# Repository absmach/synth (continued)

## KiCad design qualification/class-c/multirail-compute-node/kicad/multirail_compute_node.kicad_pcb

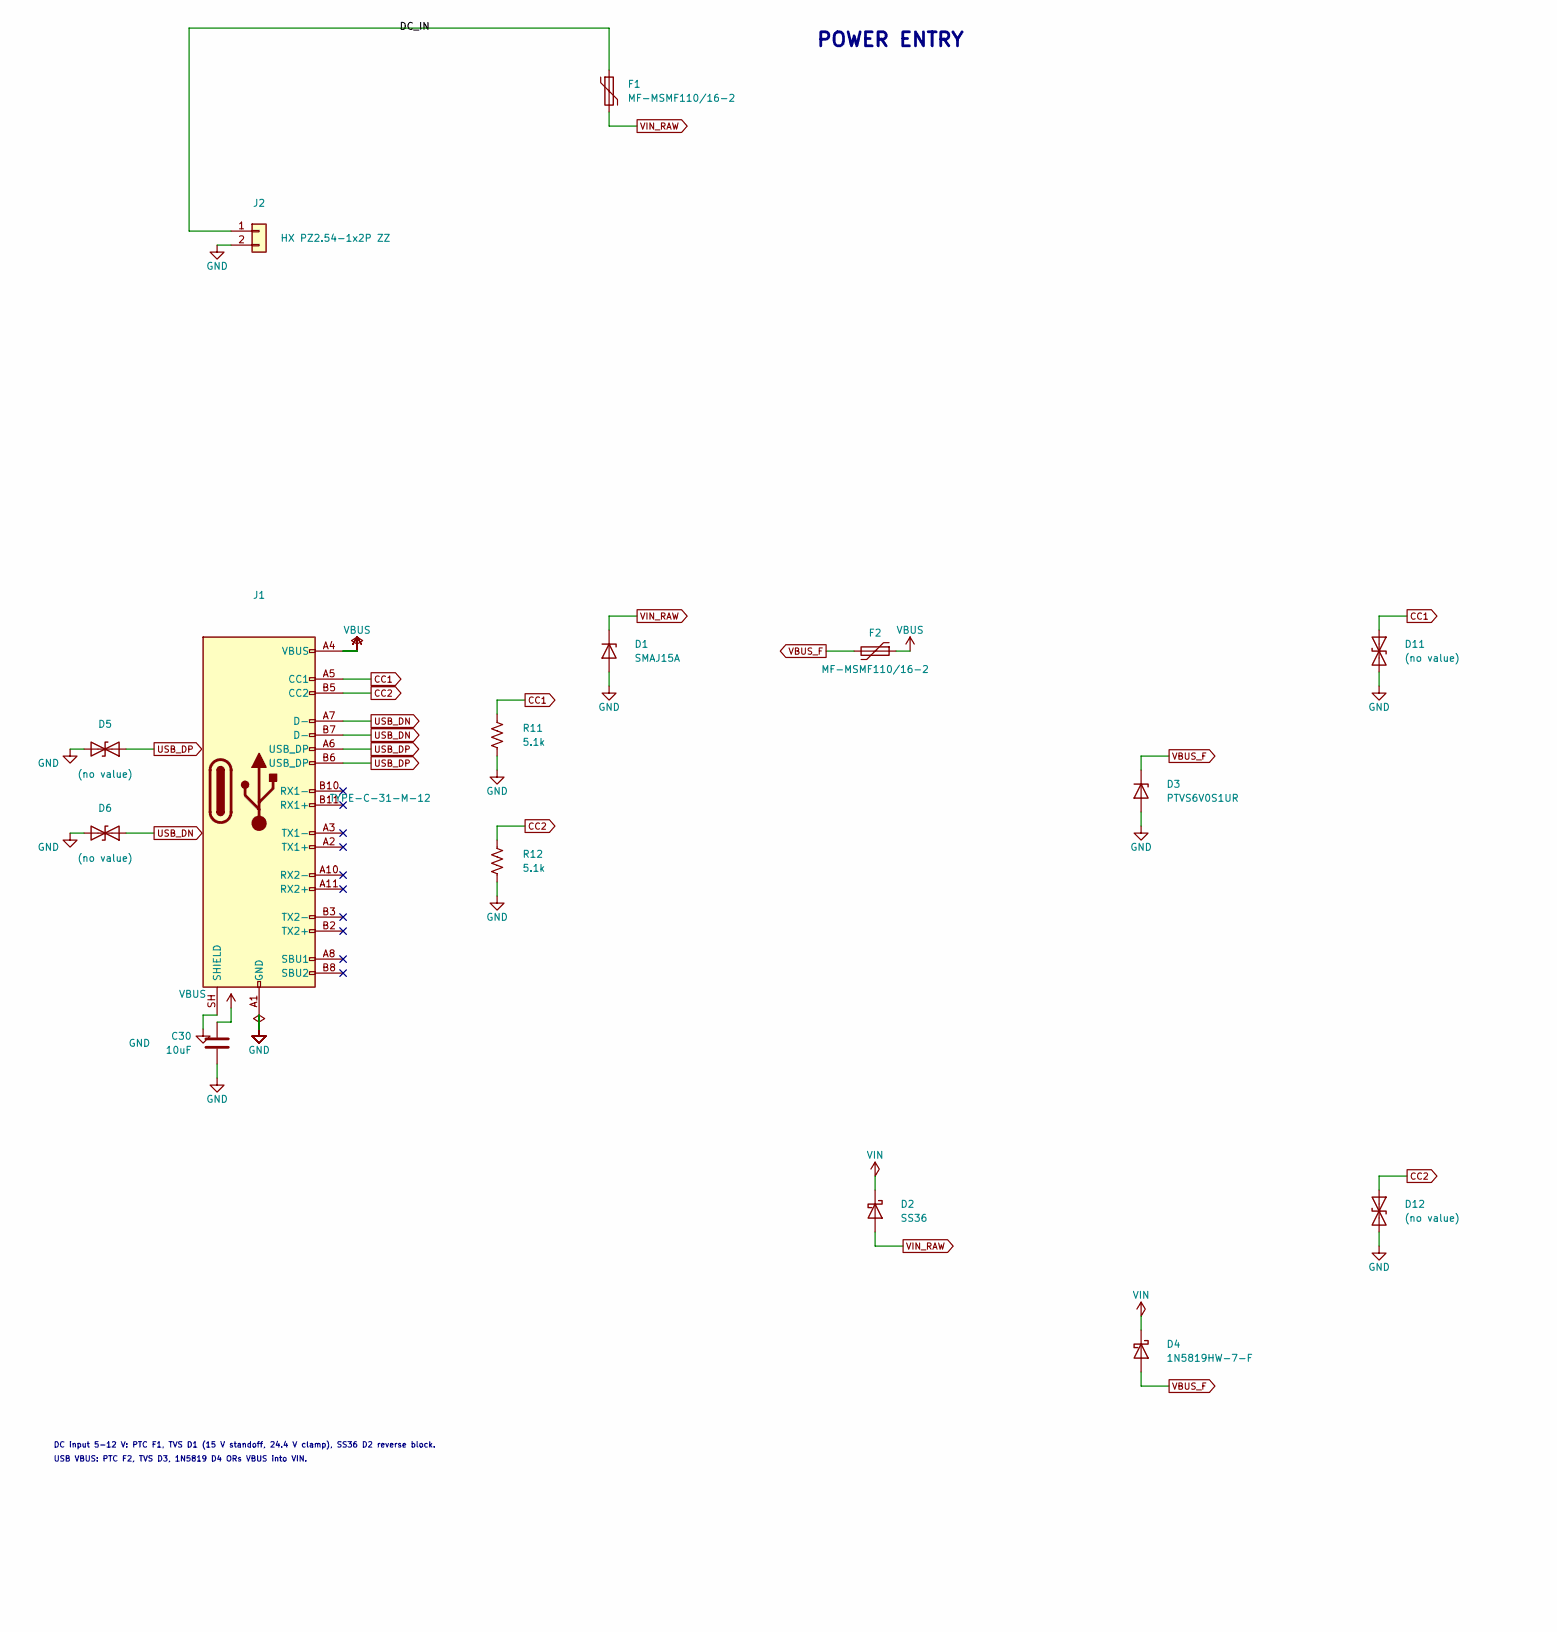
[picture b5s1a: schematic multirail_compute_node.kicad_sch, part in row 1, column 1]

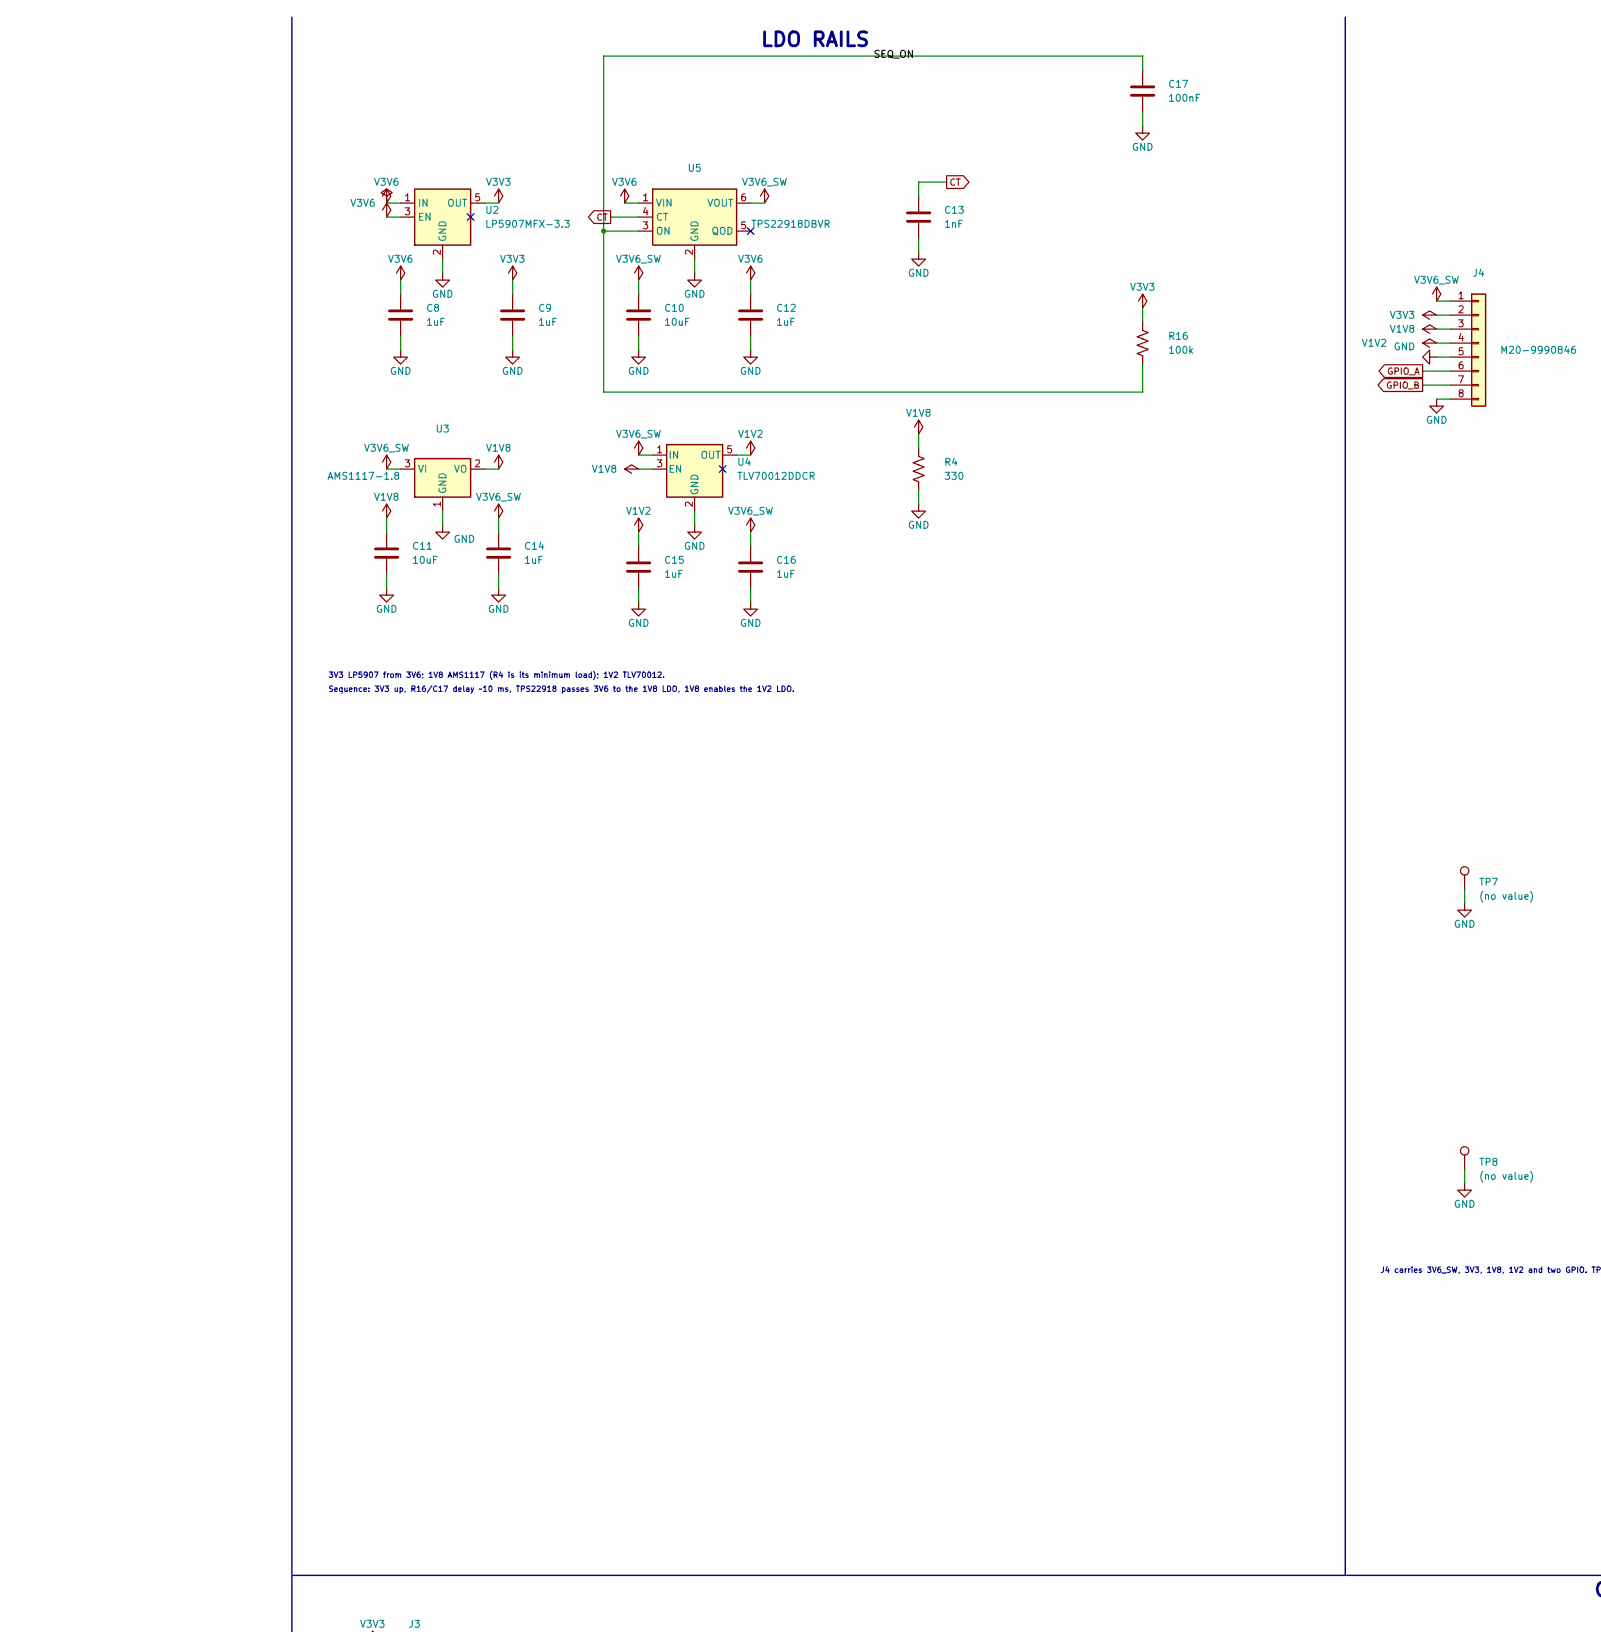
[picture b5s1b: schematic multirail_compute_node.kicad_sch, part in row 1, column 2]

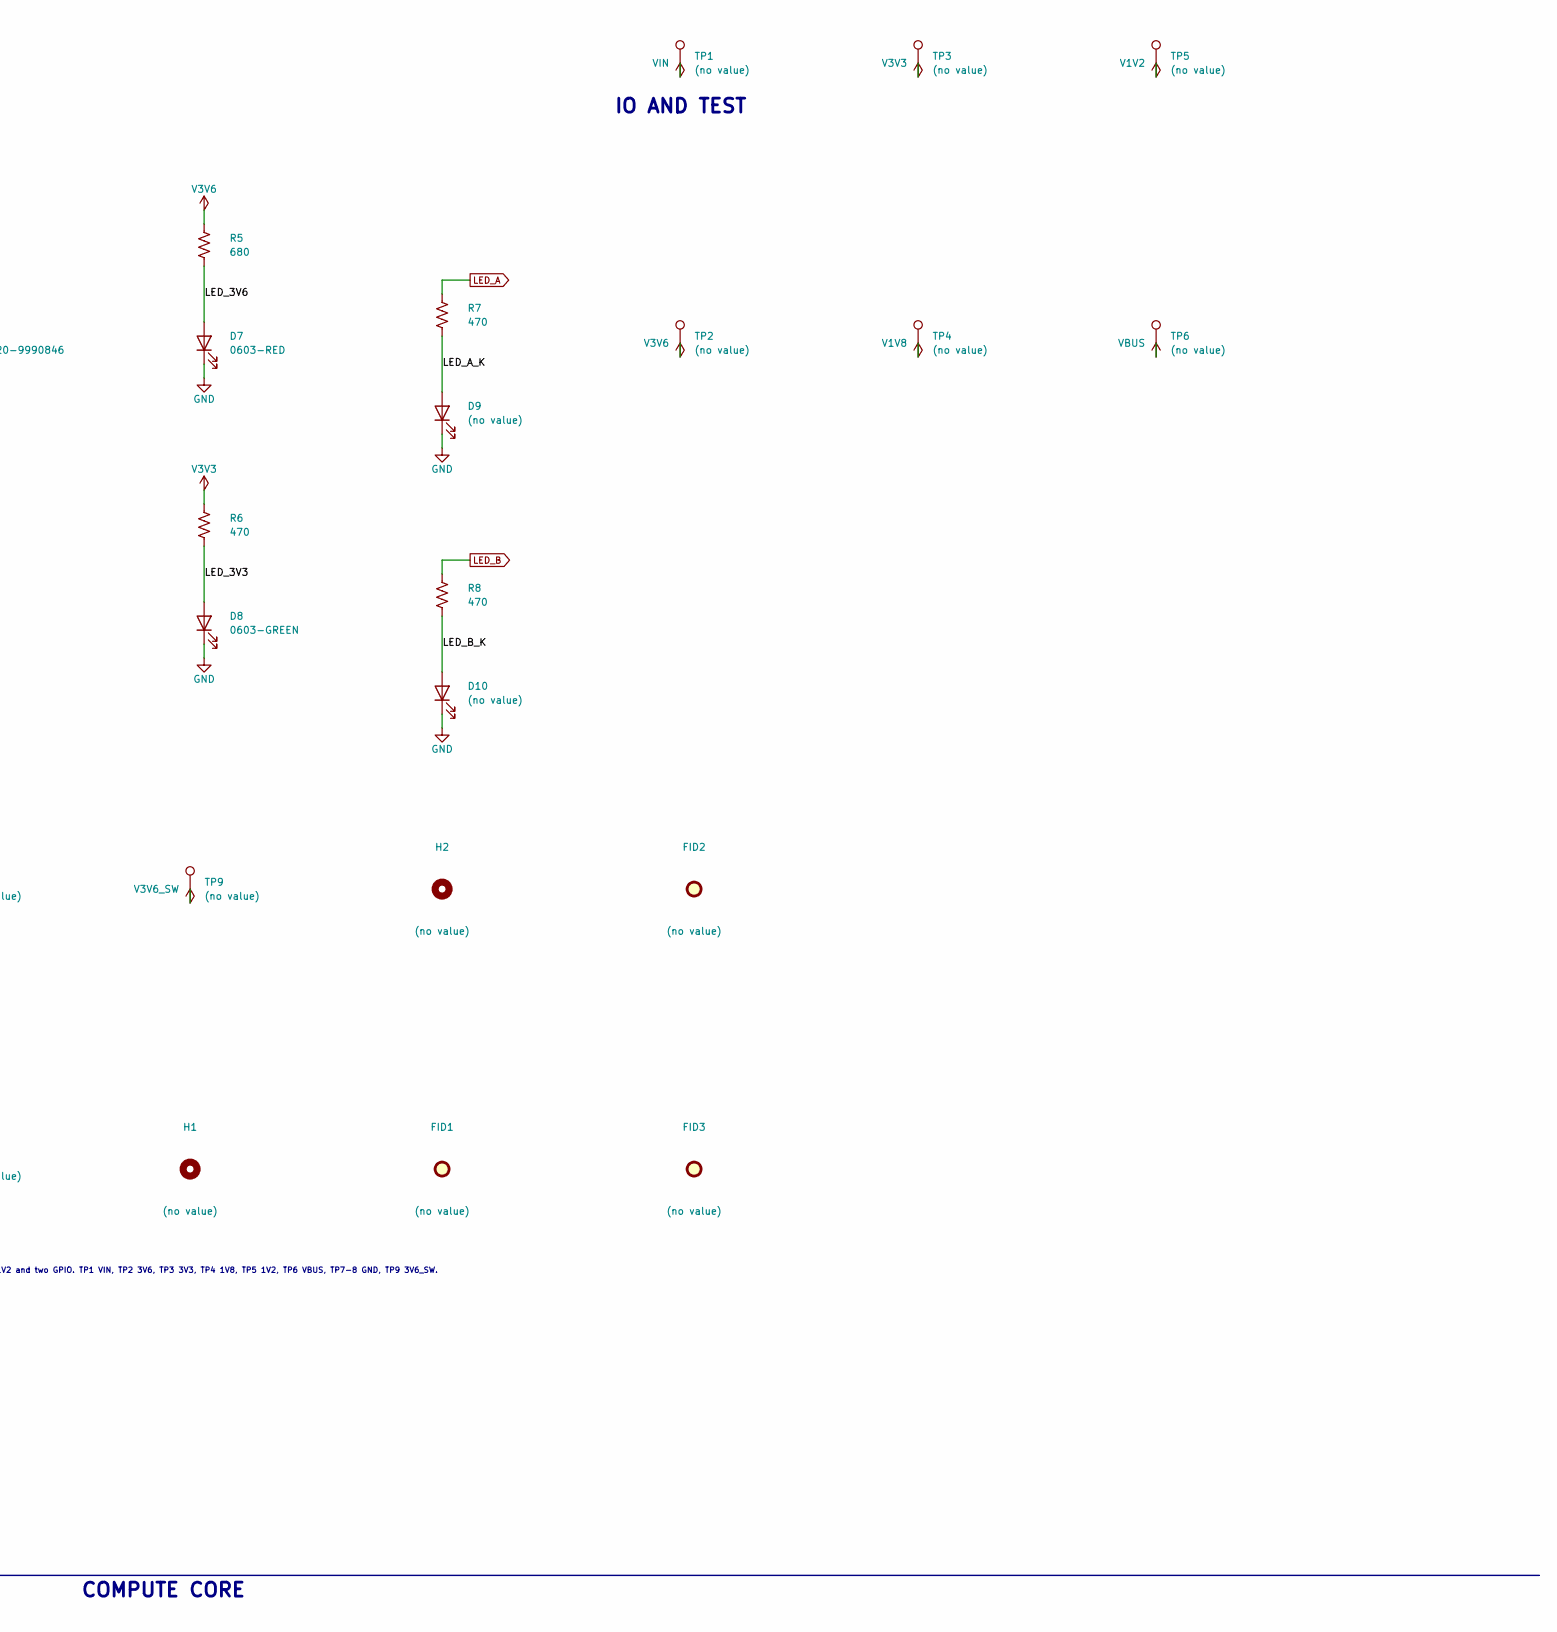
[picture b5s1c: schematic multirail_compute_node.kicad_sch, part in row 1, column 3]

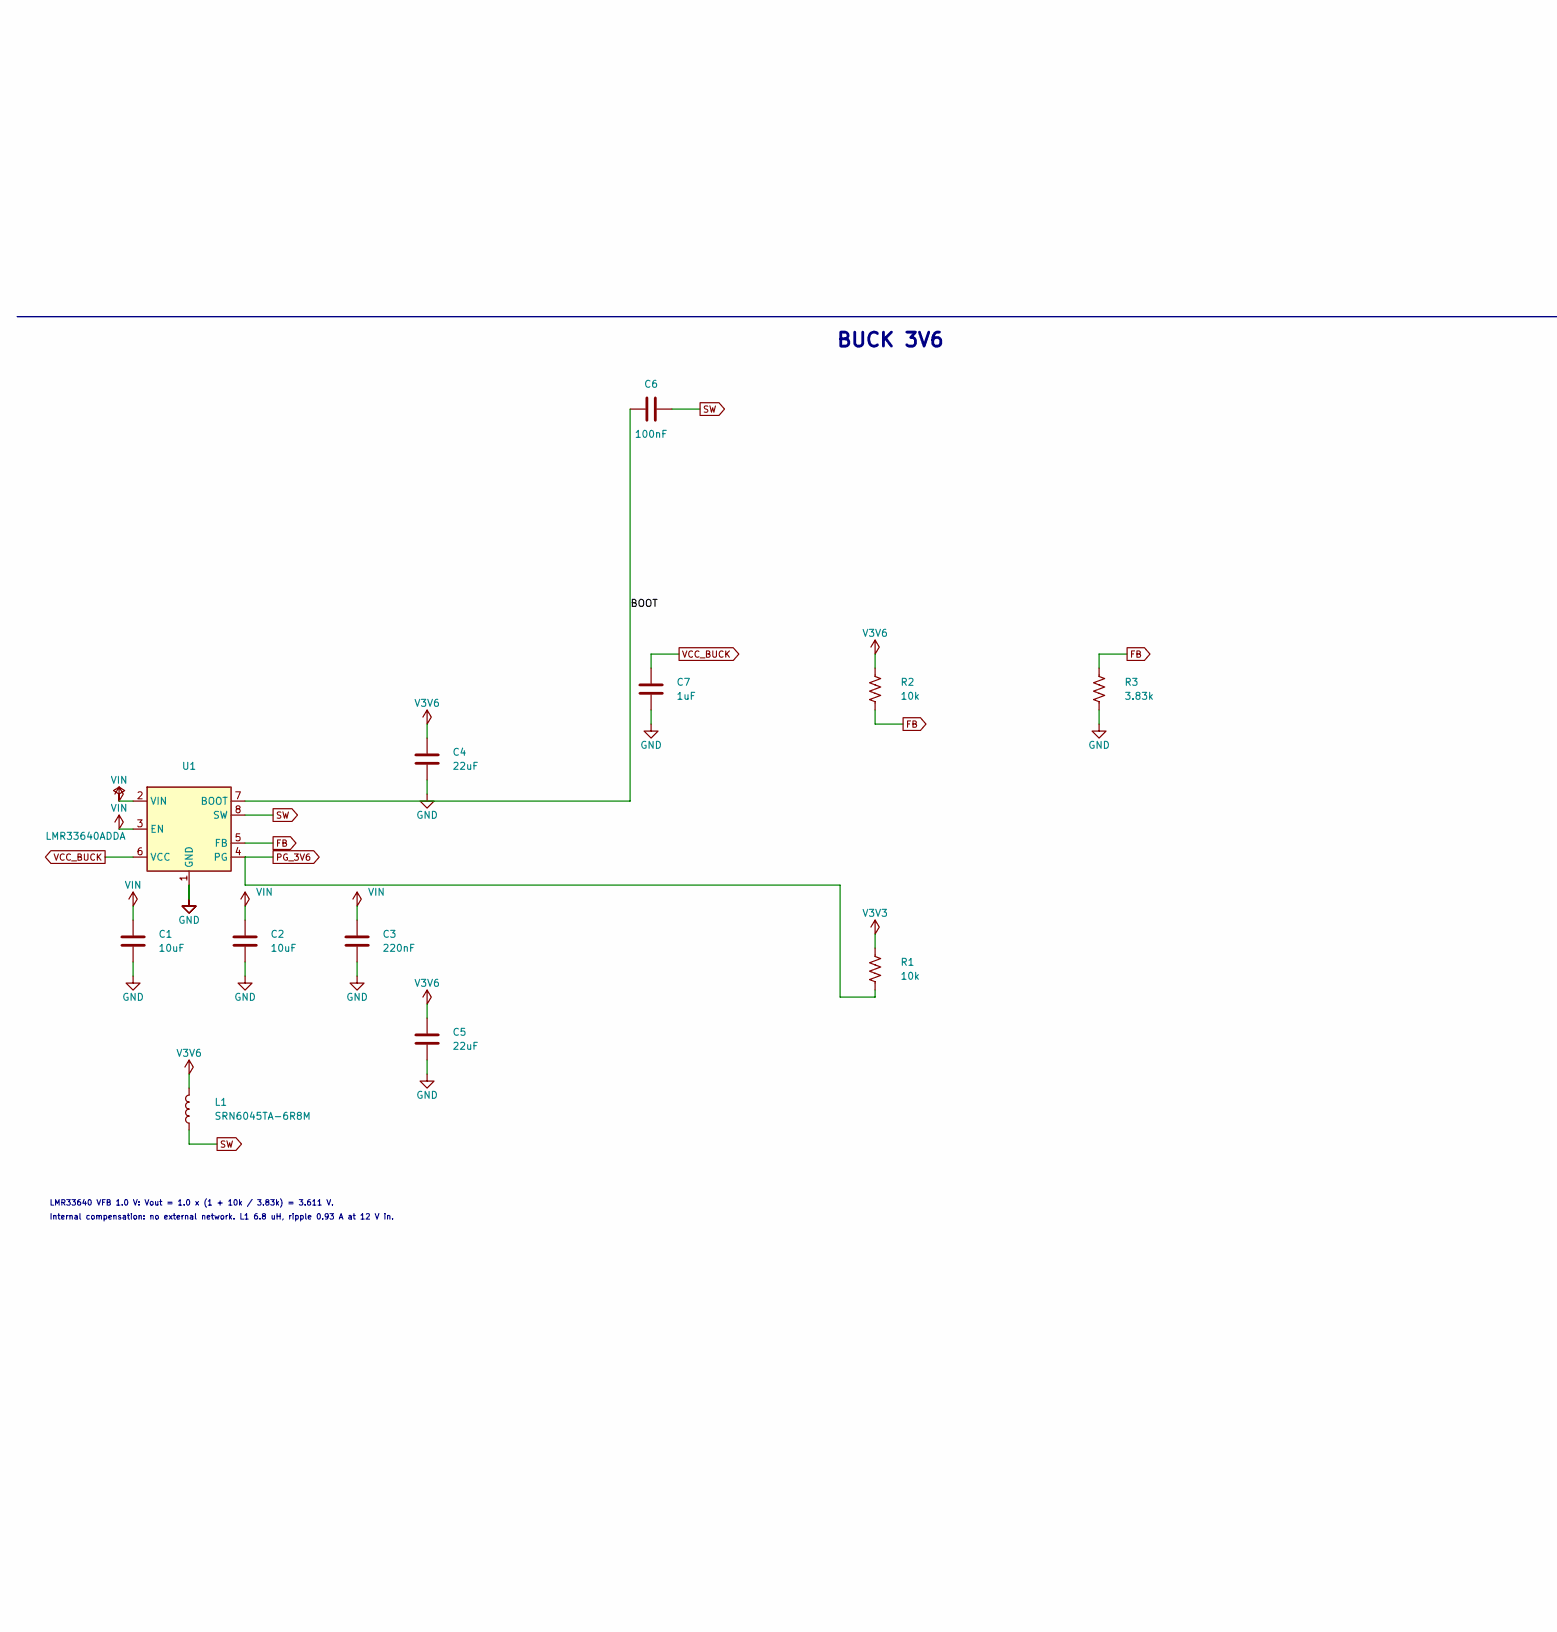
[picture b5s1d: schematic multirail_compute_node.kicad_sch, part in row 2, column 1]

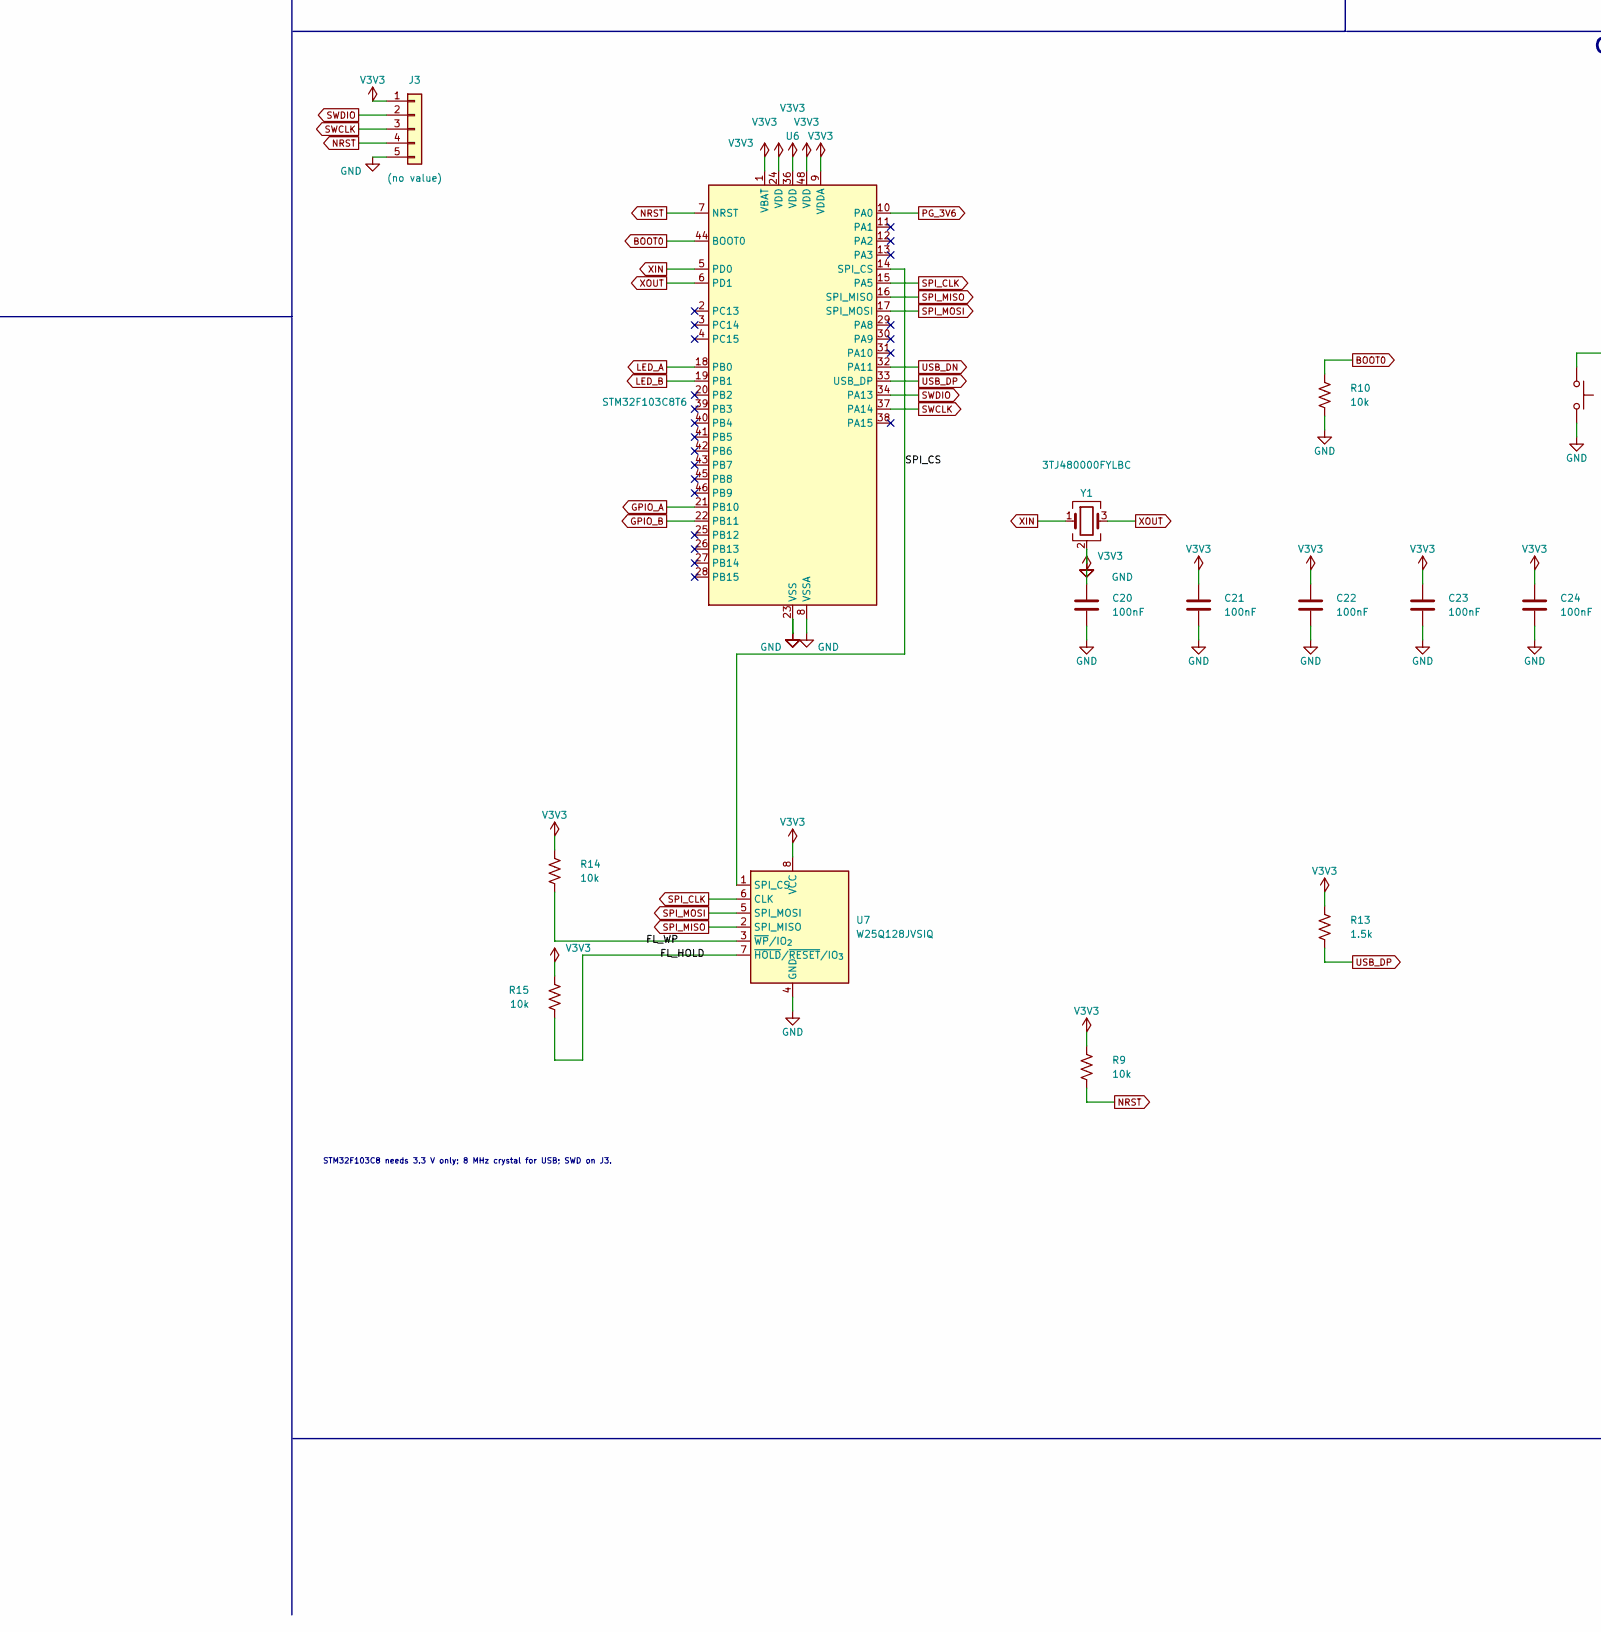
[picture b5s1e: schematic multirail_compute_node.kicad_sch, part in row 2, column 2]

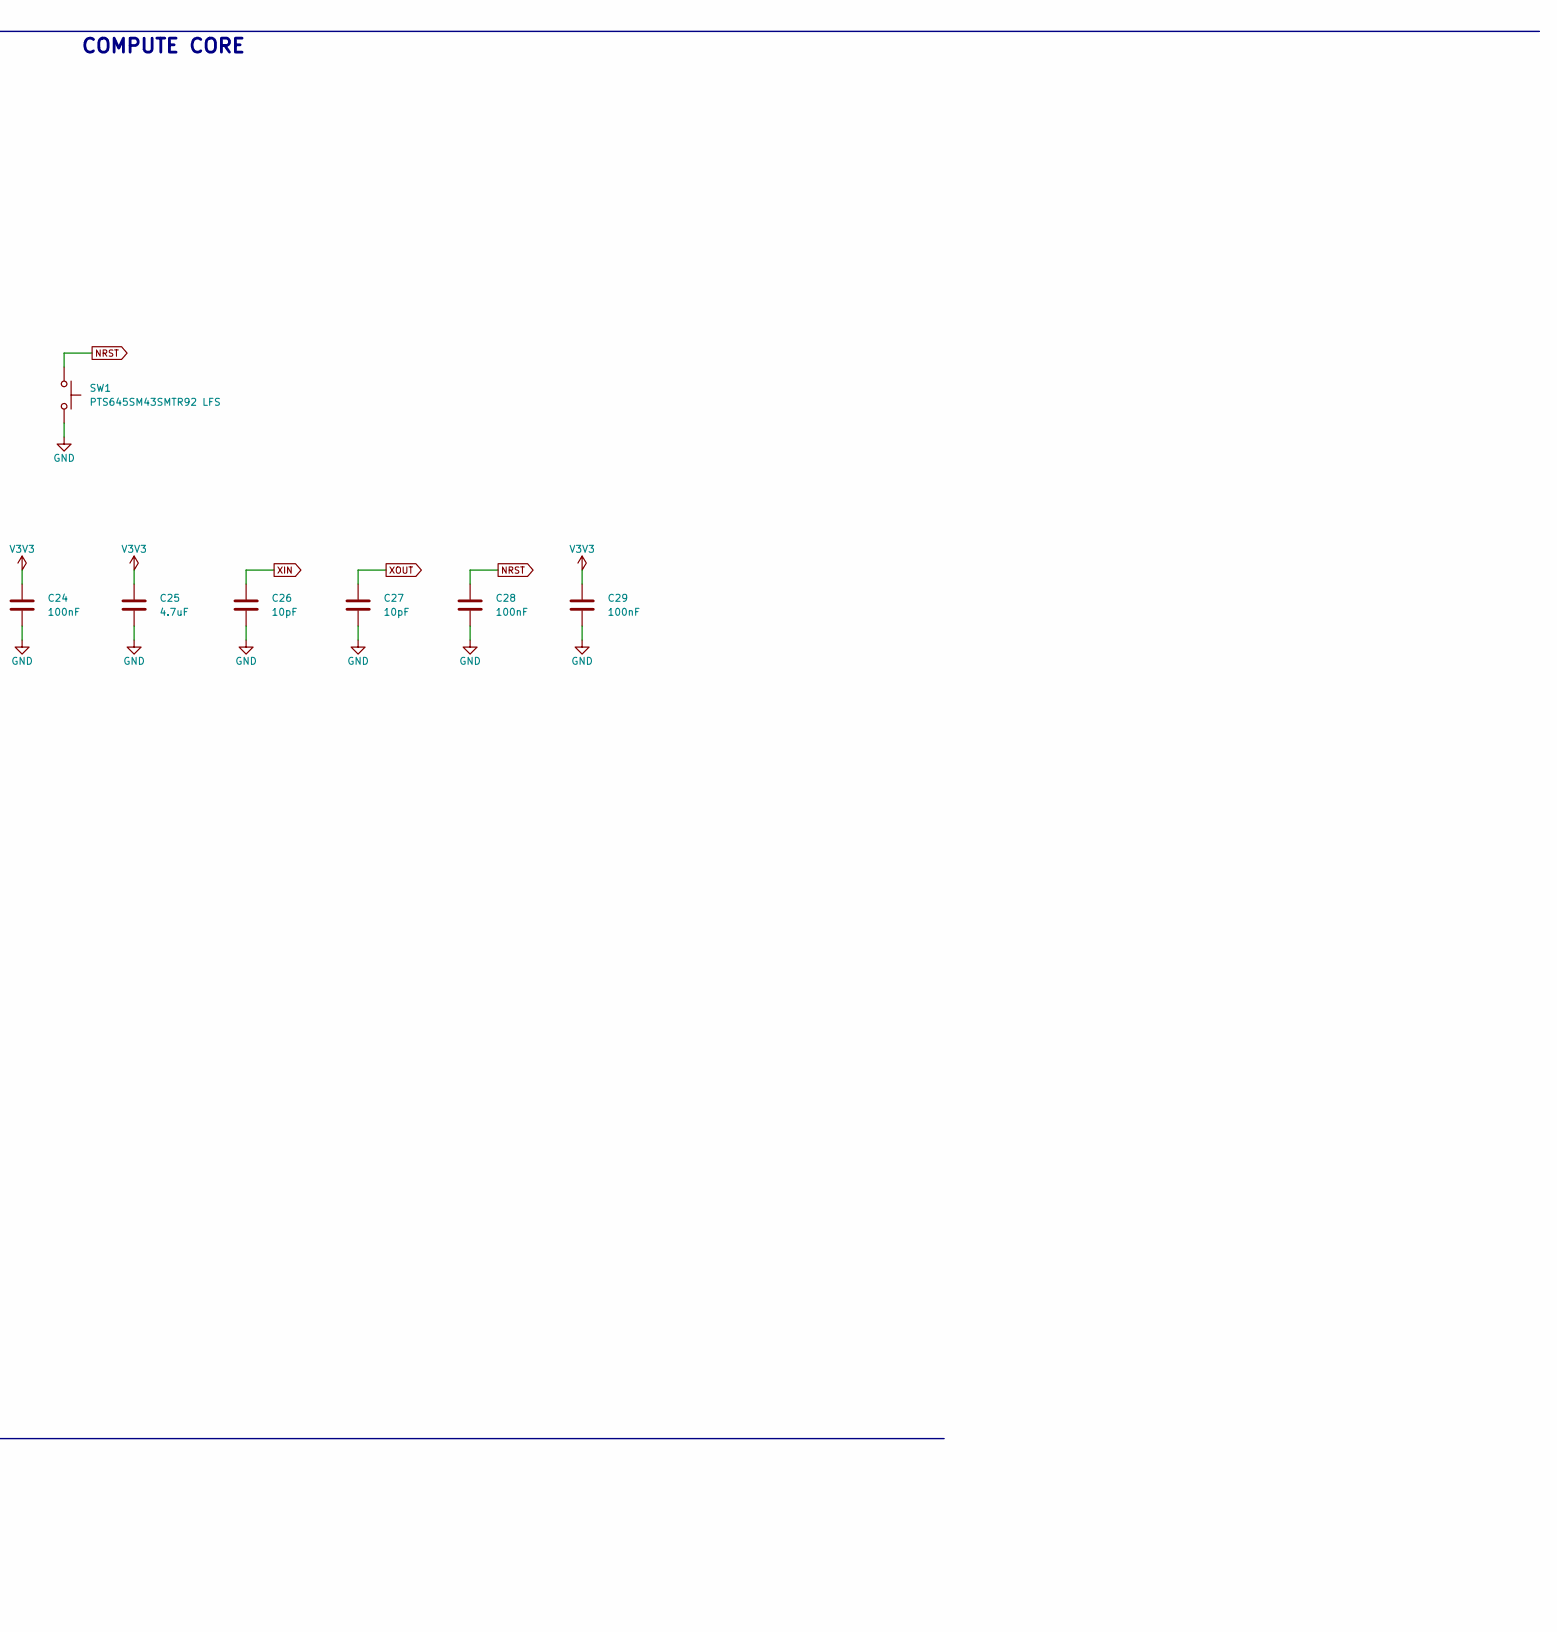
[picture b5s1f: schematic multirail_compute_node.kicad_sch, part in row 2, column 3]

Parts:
C1, C2: 10uF; C_1206_3216Metric
C3: 220nF; C_0603_1608Metric
C4, C5: 22uF; C_0805_2012Metric
C6, C17, C20, C21, C22, C23, C24, C28, C29: 100nF; C_0603_1608Metric
C7, C8, C9, C12, C14, C15, C16: 1uF; C_0603_1608Metric
C10, C11, C30: 10uF; C_0805_2012Metric
C13: 1nF; C_0603_1608Metric
C25: 4.7uF; C_0805_2012Metric
C26, C27: 10pF; C_0603_1608Metric
D1: SMAJ15A; D_SMA; MPN SMAJ15A
D2: SS36; D_SMC; MPN SS36
D3: PTVS6V0S1UR; Nexperia_CFP3_SOD-123W; MPN PTVS6V0S1UR
D4: 1N5819HW-7-F; D_SOD-123; MPN 1N5819HW-7-F; LCSC C82544
D5, D6, D11, D12: (no value); D_SOD-323
D7: 0603-RED; LED_0603_1608Metric; MPN 0603-RED; LCSC C2286
D8: 0603-GREEN; LED_0603_1608Metric; MPN 0603-GREEN; LCSC C72043
D9, D10: (no value); LED_0603_1608Metric
F1, F2: MF-MSMF110/16-2; Fuse_1812_4532Metric; MPN MF-MSMF110/16-2; LCSC C210834
FID1, FID2, FID3: (no value); Fiducial_1mm_Mask2mm
H1, H2: (no value); MountingHole_2.5mm
J1: TYPE-C-31-M-12; USB_C_Receptacle_HRO_TYPE-C-31-M-12; MPN TYPE-C-31-M-12; LCSC C165948
J2: HX PZ2.54-1x2P ZZ; PinHeader_1x02_P2.54mm_Vertical; MPN HX PZ2.54-1x2P ZZ; LCSC C32713268
J3: (no value); PinHeader_1x05_P2.54mm_Vertical
J4: M20-9990846; PinHeader_1x08_P2.54mm_Vertical; MPN M20-9990846
L1: SRN6045TA-6R8M; L_Bourns_SRN6045TA; MPN SRN6045TA-6R8M
R1, R2, R9, R10, R14, R15: 10k; R_0603_1608Metric
R3: 3.83k; R_0603_1608Metric
R4: 330; R_0603_1608Metric
R5: 680; R_0603_1608Metric
R6, R7, R8: 470; R_0603_1608Metric
R11, R12: 5.1k; R_0603_1608Metric
R13: 1.5k; R_0603_1608Metric
R16: 100k; R_0603_1608Metric
SW1: PTS645SM43SMTR92 LFS; SW_SPST_PTS645Sx43SMTR92; MPN PTS645SM43SMTR92 LFS; LCSC C221880
TP1, TP2, TP3, TP4, TP5, TP6, TP7, TP8, TP9: (no value); TestPoint_Pad_D1.5mm
U1: LMR33640ADDA; HSOP-8-1EP_3.9x4.9mm_P1.27mm_EP2.41x3.1mm; MPN LMR33640ADDA
U2: LP5907MFX-3.3; SOT-23-5; MPN LP5907MFX-3.3; LCSC C83437
U3: AMS1117-1.8; SOT-223-3_TabPin2; MPN AMS1117-1.8; LCSC C6188
U4: TLV70012DDCR; TSOT-23-5; MPN TLV70012DDCR
U5: TPS22918DBVR; SOT-23-6; MPN TPS22918DBVR; LCSC C131941
U6: STM32F103C8T6; LQFP-48_7x7mm_P0.5mm; MPN STM32F103C8T6; LCSC C8734
U7: W25Q128JVSIQ; SOIC-8_5.3x5.3mm_P1.27mm; MPN W25Q128JVSIQ; LCSC C97521
Y1: 3TJ480000FYLBC; Crystal_SMD_3225-4Pin_3.2x2.5mm; MPN 3TJ480000FYLBC

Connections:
BOOT: C6.1, U1.7 (BOOT)
BOOT0: R10.1, U6.44 (BOOT0)
CC1: D11.1 (A1), J1.A5 (CC1), R11.1
CC2: D12.1 (A1), J1.B5 (CC2), R12.1
CT: C13.1, U5.4 (CT)
DC_IN: F1.1, J2.1
FB: R2.2, R3.1, U1.5 (FB)
FL_HOLD: R15.1, U7.7 (~HOLD/~RESET/IO_{3})
FL_WP: R14.1, U7.3 (~WP/IO_{2})
GND: C1.2, C2.2, C3.2, C4.2, C5.2, C7.2, C8.2, C9.2, C10.2, C11.2, C12.2, C13.2, C14.2, C15.2, C16.2, C17.2, C20.2, C21.2, C22.2, C23.2, C24.2, C25.2, C26.2, C27.2, C28.2, C29.2, C30.2, D1.2 (A), D3.2 (A), D5.2 (A2), D6.2 (A2), D7.1 (K), D8.1 (K), D9.1 (K), D10.1 (K), D11.2 (A2), D12.2 (A2), J1.A1 (GND), J1.A12 (GND), J1.B1 (GND), J1.B12 (GND), J1.SH (SHIELD), J2.2, J3.5, J4.5, J4.8, R3.2, R4.2, R10.2, R11.2, R12.2, SW1.2, TP7.1, TP8.1, U1.1 (GND), U1.9 (GND), U2.2 (GND), U3.1 (GND), U4.2 (GND), U5.2 (GND), U6.8 (VSSA), U6.23 (VSS), U6.35 (VSS), U6.47 (VSS), U7.4 (GND), Y1.2 (G), Y1.4 (G)
GPIO_A: J4.6, U6.21 (PB10)
GPIO_B: J4.7, U6.22 (PB11)
LED_3V3: D8.2 (A), R6.2
LED_3V6: D7.2 (A), R5.2
LED_A: R7.1, U6.18 (PB0)
LED_A_K: D9.2 (A), R7.2
LED_B: R8.1, U6.19 (PB1)
LED_B_K: D10.2 (A), R8.2
NRST: C28.1, J3.4, R9.2, SW1.1, U6.7 (NRST)
PG_3V6: R1.1, U1.4 (PG), U6.10 (PA0)
SEQ_ON: C17.1, R16.2, U5.3 (ON)
SPI_CLK: U6.15 (PA5), U7.6 (CLK)
SPI_CS: U6.14 (PA4), U7.1 (~CS)
SPI_MISO: U6.16 (PA6), U7.2 (DO/IO_{1})
SPI_MOSI: U6.17 (PA7), U7.5 (DI/IO_{0})
SW: C6.2, L1.1, U1.8 (SW)
SWCLK: J3.3, U6.37 (PA14)
SWDIO: J3.2, U6.34 (PA13)
USB_DN: D6.1 (A1), J1.A7 (D-), J1.B7 (D-), U6.32 (PA11)
USB_DP: D5.1 (A1), J1.A6 (D+), J1.B6 (D+), R13.2, U6.33 (PA12)
V1V2: C15.1, J4.4, TP5.1, U4.5 (OUT)
V1V8: C11.1, J4.3, R4.1, TP4.1, U3.2 (VO), U4.3 (EN)
V3V3: C9.1, C20.1, C21.1, C22.1, C23.1, C24.1, C25.1, C29.1, J3.1, J4.2, R1.2, R6.1, R9.1, R13.1, R14.2, R15.2, R16.1, TP3.1, U2.5 (OUT), U6.1 (VBAT), U6.9 (VDDA), U6.24 (VDD), U6.36 (VDD), U6.48 (VDD), U7.8 (VCC)
V3V6: C4.1, C5.1, C8.1, C12.1, L1.2, R2.1, R5.1, TP2.1, U2.1 (IN), U2.3 (EN), U5.1 (VIN)
V3V6_SW: C10.1, C14.1, C16.1, J4.1, TP9.1, U3.3 (VI), U4.1 (IN), U5.6 (VOUT)
VBUS: C30.1, F2.1, J1.A4 (VBUS), J1.A9 (VBUS), J1.B4 (VBUS), J1.B9 (VBUS), TP6.1
VBUS_F: D3.1 (K), D4.2 (A), F2.2
VCC_BUCK: C7.1, U1.6 (VCC)
VIN: C1.1, C2.1, C3.1, D2.1 (K), D4.1 (K), TP1.1, U1.2 (VIN), U1.3 (EN)
VIN_RAW: D1.1 (K), D2.2 (A), F1.2
XIN: C26.1, U6.5 (PD0), Y1.1
XOUT: C27.1, U6.6 (PD1), Y1.3

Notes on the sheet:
POWER ENTRY
BUCK 3V6
LDO RAILS
COMPUTE CORE
IO AND TEST
DC input 5-12 V: PTC F1, TVS D1 (15 V standoff, 24.4 V clamp), SS36 D2 reverse block.
USB VBUS: PTC F2, TVS D3, 1N5819 D4 ORs VBUS into VIN.
LMR33640 VFB 1.0 V: Vout = 1.0 x (1 + 10k / 3.83k) = 3.611 V.
Internal compensation: no external network. L1 6.8 uH, ripple 0.93 A at 12 V in.
3V3 LP5907 from 3V6; 1V8 AMS1117 (R4 is its minimum load); 1V2 TLV70012.
Sequence: 3V3 up, R16/C17 delay ~10 ms, TPS22918 passes 3V6 to the 1V8 LDO, 1V8 enables the 1V2 LDO.
STM32F103C8 needs 3.3 V only; 8 MHz crystal for USB; SWD on J3.
J4 carries 3V6_SW, 3V3, 1V8, 1V2 and two GPIO. TP1 VIN, TP2 3V6, TP3 3V3, TP4 1V8, TP5 1V2, TP6 VBUS, TP7-8 GND, TP9 3V6_SW.

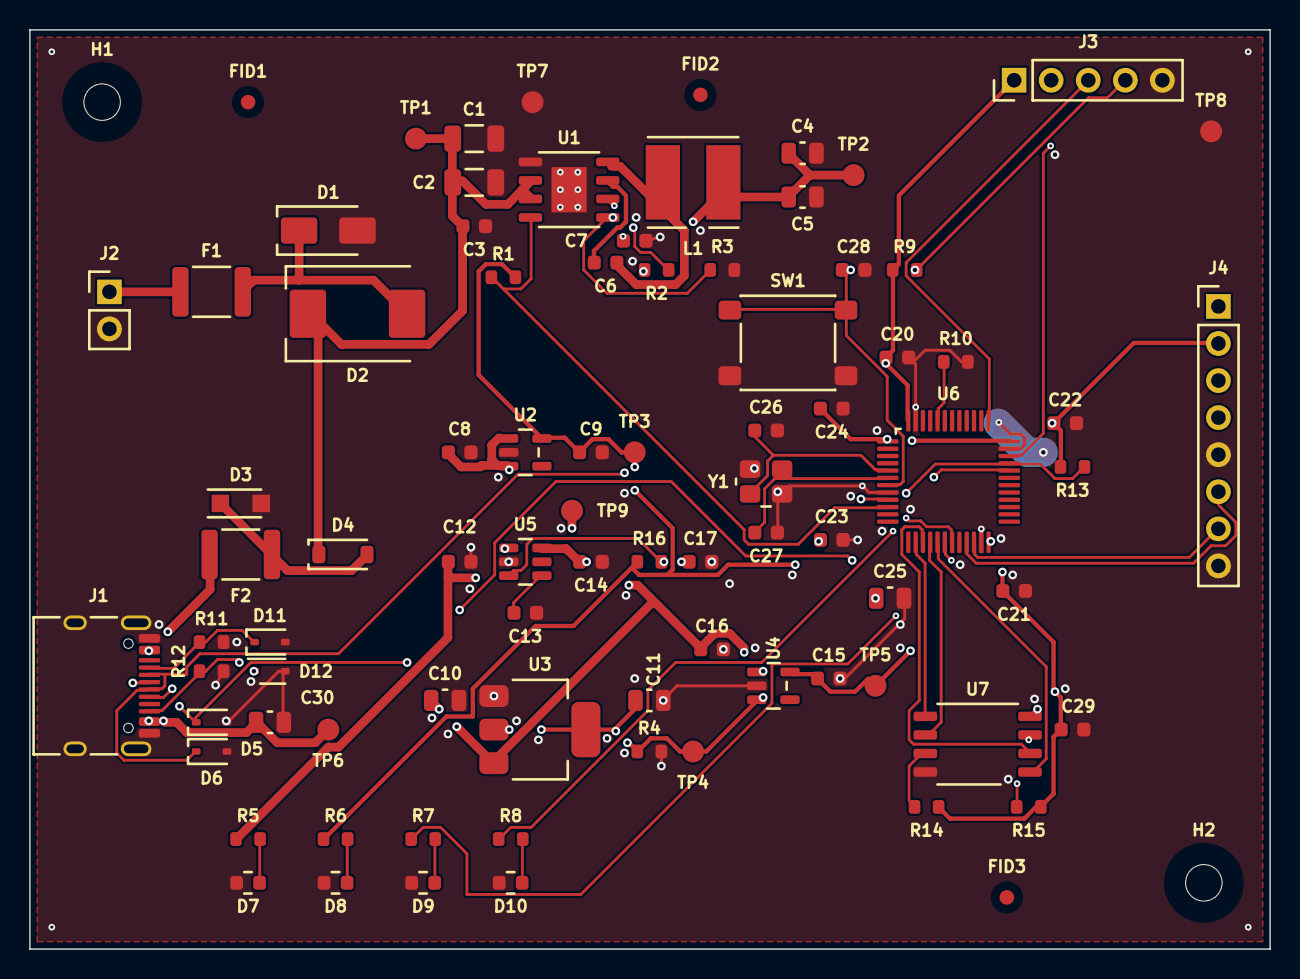
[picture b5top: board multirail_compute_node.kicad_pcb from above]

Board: 4 copper layers, 85.0 x 63.0 mm, 86 parts (0 on the bottom side), 42 nets.

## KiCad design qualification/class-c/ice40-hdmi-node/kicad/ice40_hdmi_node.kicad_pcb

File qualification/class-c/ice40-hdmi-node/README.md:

# iCE40HX4K HDMI (DVI-style TMDS) node (Class C, case 3)

An iCE40HX4K FPGA in a 144-pin TQFP (0.5 mm pitch) driving an HDMI Type-A receptacle with four TMDS-style differential pairs (three data lanes and the clock) through 270 ohm source resistors, with the DDC lines level-shifted, a hot-plug-detect divider and a fused +5 V pin, an SPI boot flash and four status LEDs, powered from a 5 V terminal, on six copper layers. It answers #330 under #40: a board whose high-speed differential interface declares impedance, pair spacing and skew, with the delivered copper measured against those declarations. The interface is DVI-style: the iCE40 cannot source TMDS levels, so each line is an LVCMOS33 output through a series resistor into the sink's 50 ohm termination to 3.3 V. No HDMI compliance is claimed; the board demonstrates only what is measured below.

## The board

| Group | Parts |
|---|---|
| Power entry | `J1` JST B2B-XH-A 2-pin header (5 V in); `F1` Bourns MF-MSMF110/16-2 (1.1 A hold, 2.2 A trip, 16 V); `D1` Nexperia PTVS6V0S1UR (6.0 V standoff above the 5.5 V maximum input, 6.67 V minimum breakdown); `D2` Vishay SS36 Schottky (60 V, 3 A) as the reverse-polarity stage; `C1`, `TP1` |
| 3.3 V | `U1` AMS1117-3.3 with 10 uF capacitors `C2` to `C5` |
| 1.2 V core | `U2` Texas Instruments TLV70012DDCR, TSOT-23-5, with `C6` and `C7`; the PLL supplies `VCCPLL0` and `VCCPLL1` through the ferrite beads `L1` and `L2` and `C21`, `C22` |
| FPGA | `U3` Lattice iCE40HX4K-TQ144, supply decoupling 100 nF `C10` to `C20` and `C25` to `C27`; `X1` SiTime SiT8008 25 MHz oscillator with `C23` |
| Configuration | `U4` Winbond W25Q128JVSIQ, SOIC-8 208 mil, master SPI; `R30` and `R31` pull `CDONE` and `CRESET_B` up, `R32` and `R33` the write-protect and hold pins |
| HDMI | `J2` Amphenol 10029449-111RLF HDMI Type-A receptacle; `R1` to `R8` 270 ohm source resistors; `D3` onsemi SRV05-4 4-line ESD array on the DDC and HPD lines; `F2` Bourns MF-NSMF050-2 (0.5 A hold) on the +5 V pin; DDC level shifters `Q1` and `Q2` (IRLML6244) with `R9` and `R10` (2 k to +5 V) and `R11` and `R12` (10 k to 3.3 V); the HPD divider `R13` (10 k) and `R14` (20 k), which gives 5 V x 20 / (10 + 20) = 3.33 V at the FPGA |
| Indicators and test points | `D4` and `D5` green, `D6` and `D7` red LEDs with 470 ohm resistors `R20` to `R23`; test points `TP1` to `TP7` (+5 V, +3.3 V, +1.2 V, GND, CDONE, CRESET_B, +5 V_HDMI); two M2.5 mounting holes |

The iCE40HX4K-TQ144 has 107 user I/O (Lattice DS1040); the part model in `registry/parts/fpga/ice40hx4k_tq144.synth.toml` is built from KiCad's `FPGA_Lattice:ICE40HX4K-TQ144` symbol with the pin functions of that datasheet. The four lanes use the four adjacent pin pairs on the FPGA's left side (pins 1 and 2, 3 and 4, 7 and 8, 9 and 10), in the same top-to-bottom order as the connector's lanes, so no pair crosses another; the eight source resistors sit in one column between the FPGA and the connector.

The qualification verdict, measurements, evidence and sign-off are in [`QUALIFICATION.md`](QUALIFICATION.md); how the board was made is in [`PROVENANCE.md`](PROVENANCE.md). Gerber content hash `92d05ff69b`.

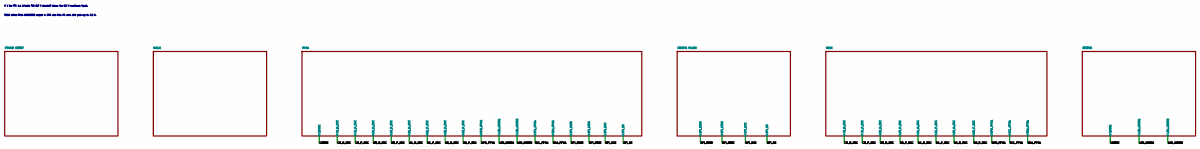
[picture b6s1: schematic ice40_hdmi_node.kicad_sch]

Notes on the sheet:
5 V in; PTC 1.1 A hold; TVS 6.0 V standoff above the 5.5 V maximum input.
TMDS drive: FPGA LVCMOS33 output + 270 ohm into 50 ohm sink pull-up to 3.3 V.

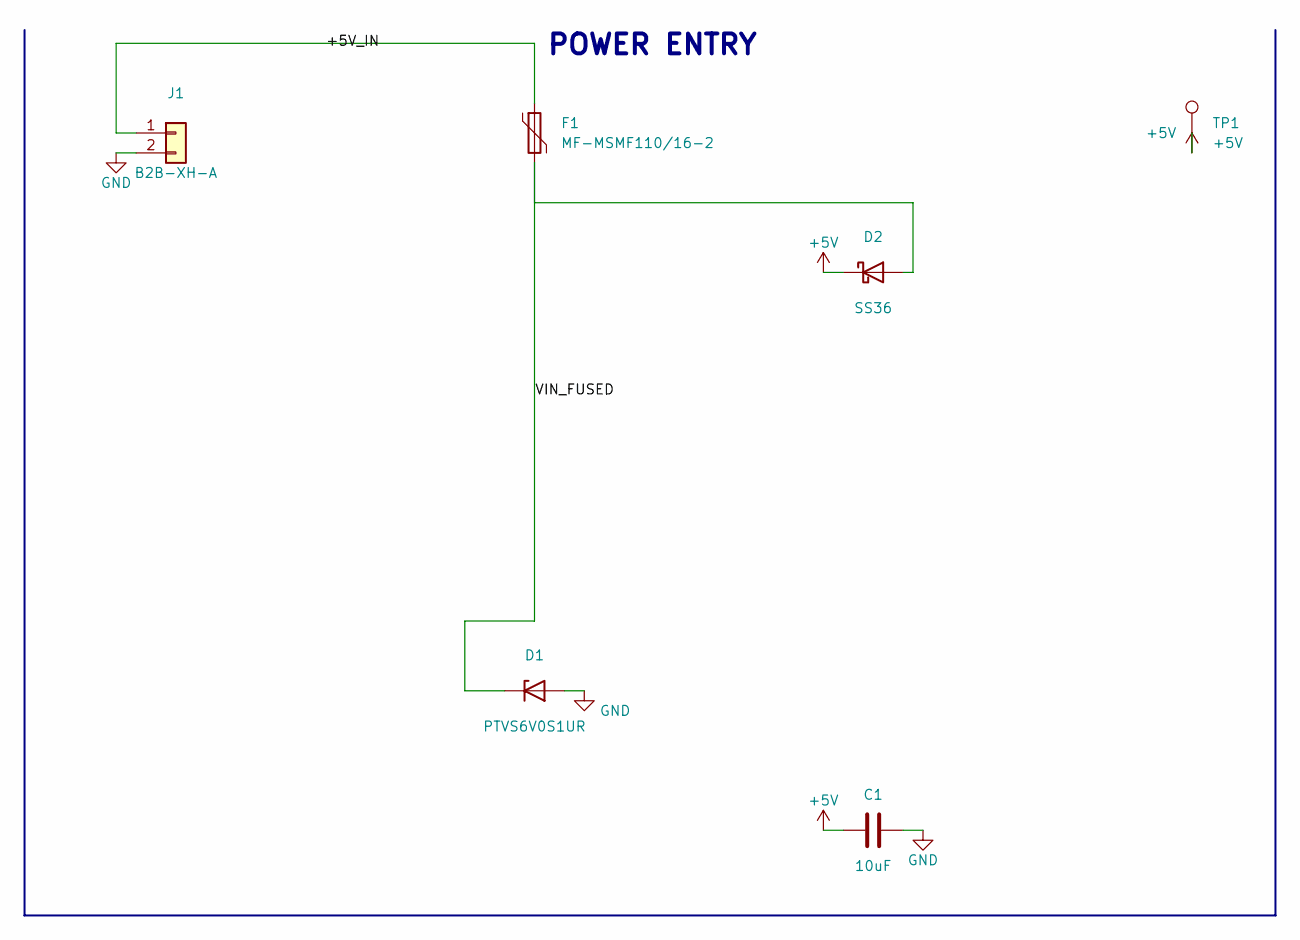
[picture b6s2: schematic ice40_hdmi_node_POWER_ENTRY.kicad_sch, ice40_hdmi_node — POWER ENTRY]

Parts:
C1: 10uF; C_0805_2012Metric
D1: PTVS6V0S1UR; Nexperia_CFP3_SOD-123W; MPN PTVS6V0S1UR
D2: SS36; D_SMC; MPN SS36
F1: MF-MSMF110/16-2; Fuse_1812_4532Metric; MPN MF-MSMF110/16-2; LCSC C210834
J1: B2B-XH-A; JST_XH_B2B-XH-A_1x02_P2.50mm_Vertical; MPN B2B-XH-A
TP1: +5V; TestPoint_Pad_D1.5mm

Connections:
+5V: C1.1, D2.1 (K), TP1.1; also elsewhere on the board
+5V_IN: F1.1, J1.1
GND: C1.2, D1.2 (A), J1.2; also elsewhere on the board
VIN_FUSED: D1.1 (K), D2.2 (A), F1.2

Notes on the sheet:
POWER ENTRY
